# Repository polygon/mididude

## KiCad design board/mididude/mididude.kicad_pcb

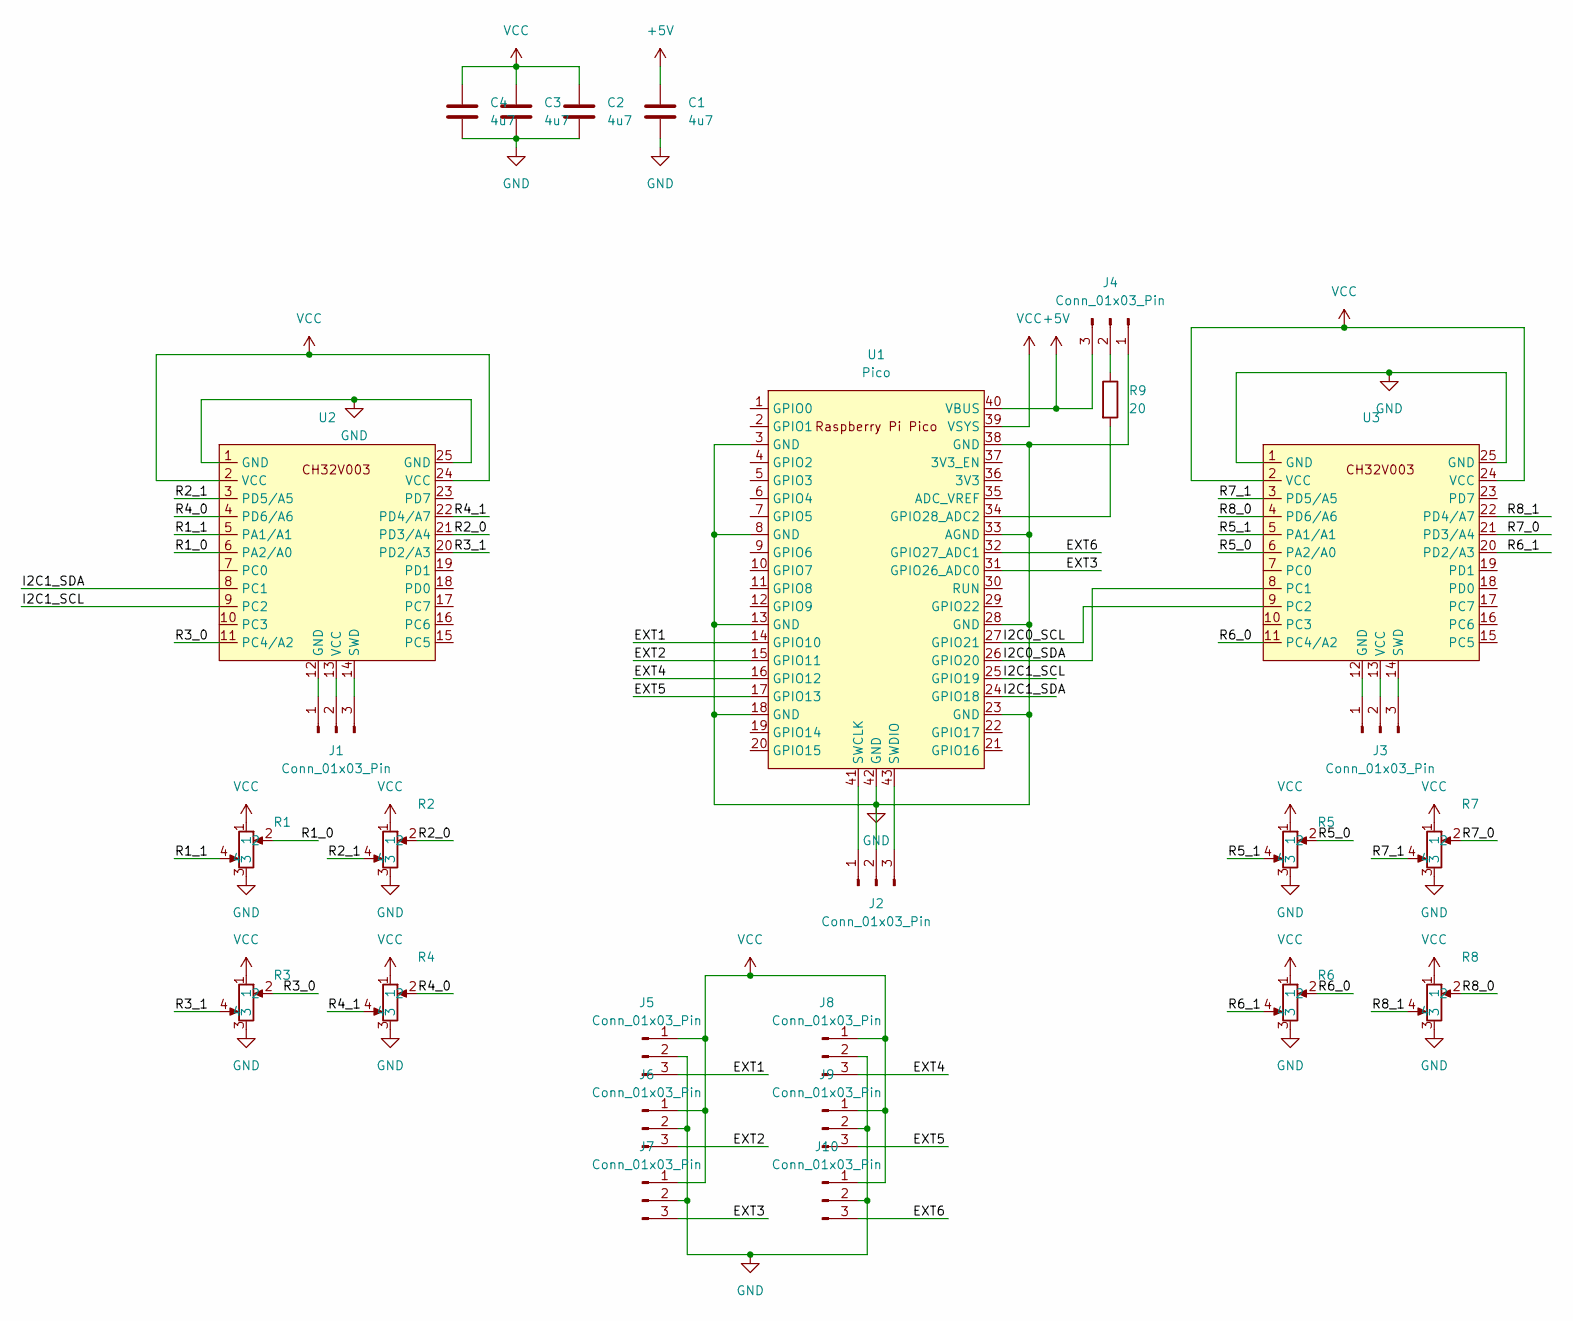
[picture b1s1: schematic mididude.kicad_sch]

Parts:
C1, C2, C3, C4: 4u7; C_0805_2012Metric_Pad1.18x1.45mm_HandSolder
J1, J2, J3, J4, J5, J6, J7, J8, J9, J10: Conn_01x03_Pin; PinHeader_1x03_P2.54mm_Vertical
R1, R2, R3, R4, R5, R6, R7, R8: Endless_potentiometer
R9: 20; R_0603_1608Metric_Pad0.98x0.95mm_HandSolder
U1: Pico; RPi_Pico_SMD_TH
U2, U3: CH32FV003 F1772

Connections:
+5V: C1.1, J4.3, U1.40 (VBUS)
/EXT1: J5.3, U1.14 (GPIO10)
/EXT2: J6.3, U1.15 (GPIO11)
/EXT3: J7.3, U1.31 (GPIO26_ADC0)
/EXT4: J8.3, U1.16 (GPIO12)
/EXT5: J9.3, U1.17 (GPIO13)
/EXT6: J10.3, U1.32 (GPIO27_ADC1)
/I2C0_SCL: U1.27 (GPIO21), U3.9 (PC2)
/I2C0_SDA: U1.26 (GPIO20), U3.8 (PC1)
/I2C1_SCL: U1.25 (GPIO19), U2.9 (PC2)
/I2C1_SDA: U1.24 (GPIO18), U2.8 (PC1)
/R1_0: R1.2, U2.6 (PA2/A0)
/R1_1: R1.4, U2.5 (PA1/A1)
/R2_0: R2.2, U2.21 (PD3/A4)
/R2_1: R2.4, U2.3 (PD5/A5)
/R3_0: R3.2, U2.11 (PC4/A2)
/R3_1: R3.4, U2.20 (PD2/A3)
/R4_0: R4.2, U2.4 (PD6/A6)
/R4_1: R4.4, U2.22 (PD4/A7)
/R5_0: R5.2, U3.6 (PA2/A0)
/R5_1: R5.4, U3.5 (PA1/A1)
/R6_0: R6.2, U3.11 (PC4/A2)
/R6_1: R6.4, U3.20 (PD2/A3)
/R7_0: R7.2, U3.21 (PD3/A4)
/R7_1: R7.4, U3.3 (PD5/A5)
/R8_0: R8.2, U3.4 (PD6/A6)
/R8_1: R8.4, U3.22 (PD4/A7)
GND: C1.2, C2.2, C3.2, C4.2, J2.2, J4.1, J5.2, J6.2, J7.2, J8.2, J9.2, J10.2, R1.3, R2.3, R3.3, R4.3, R5.3, R6.3, R7.3, R8.3, U1.3 (GND), U1.8 (GND), U1.13 (GND), U1.18 (GND), U1.23 (GND), U1.28 (GND), U1.33 (AGND), U1.38 (GND), U1.42 (GND), U2.1 (GND), U2.25 (GND), U3.1 (GND), U3.25 (GND)
unnamed: J1.1, U2.12 (GND)
unnamed: J1.2, U2.13 (VCC)
unnamed: J1.3, U2.14 (SWD)
unnamed: J2.1, U1.41 (SWCLK)
unnamed: J2.3, U1.43 (SWDIO)
unnamed: J3.1, U3.12 (GND)
unnamed: J3.2, U3.13 (VCC)
unnamed: J3.3, U3.14 (SWD)
unnamed: J4.2, R9.1
unnamed: R9.2, U1.34 (GPIO28_ADC2)
VCC: C2.1, C3.1, C4.1, J5.1, J6.1, J7.1, J8.1, J9.1, J10.1, R1.1, R2.1, R3.1, R4.1, R5.1, R6.1, R7.1, R8.1, U1.39 (VSYS), U2.2 (VCC), U2.24 (VCC), U3.2 (VCC), U3.24 (VCC)

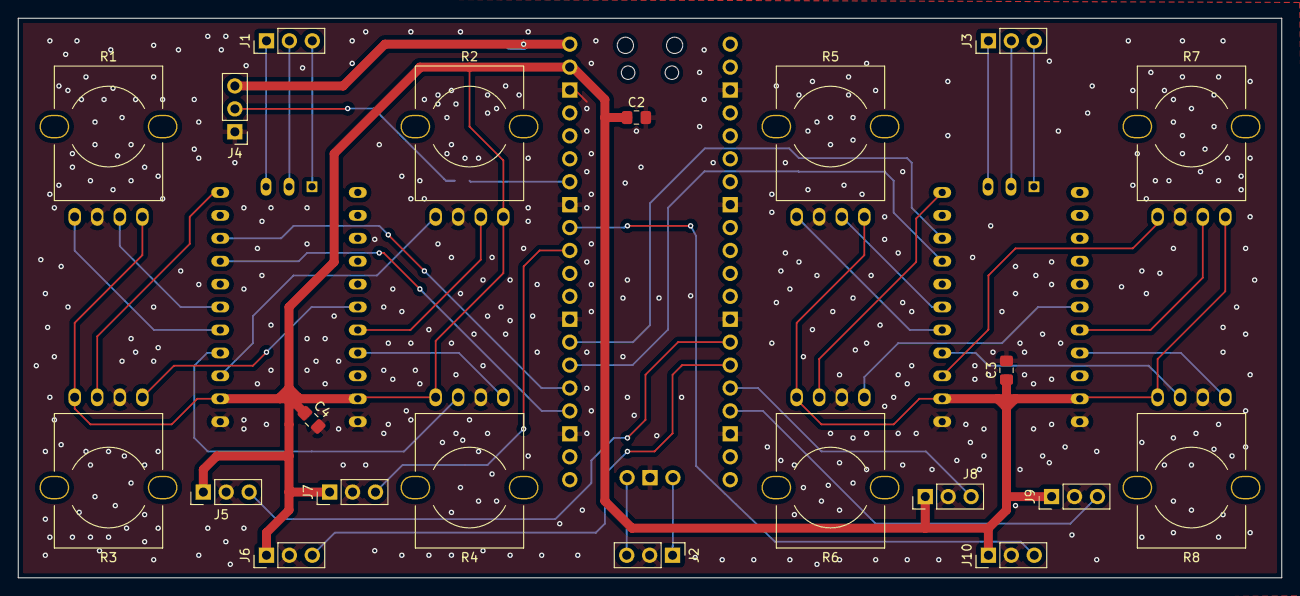
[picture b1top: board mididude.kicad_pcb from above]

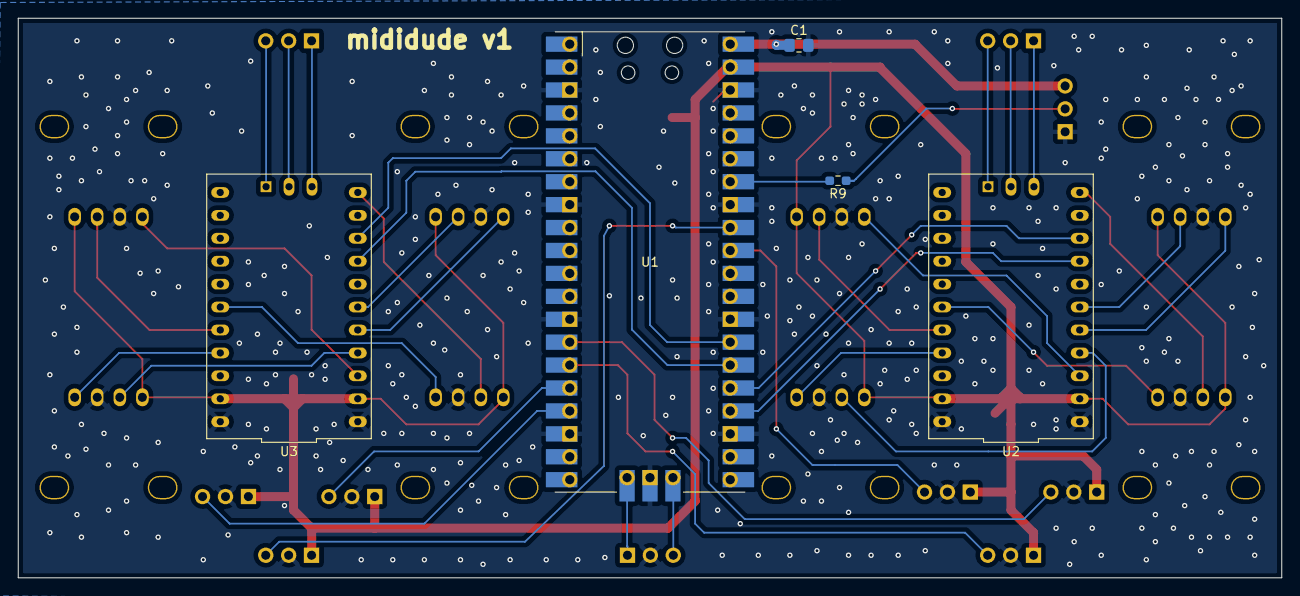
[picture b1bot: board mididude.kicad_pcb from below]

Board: 2 copper layers, 140.0 x 62.0 mm, 26 parts (5 on the bottom side), 39 nets.

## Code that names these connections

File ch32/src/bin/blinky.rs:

#![no_std]
#![no_main]
#![feature(type_alias_impl_trait)]
#![feature(impl_trait_in_assoc_type)]
#![feature(iterator_try_collect)]

use ch32_hal::adc::{Adc, AnyAdcChannel};
use ch32_hal::bind_interrupts;
use ch32_hal::peripherals::ADC1;
use ch32_hal::{self as hal, adc::AdcChannel};
use core::fmt::Write;
use core::task::Poll;
use embedded_graphics::primitives::ellipse;
use hal::usart::UartTx;

use mididude_adc::i2c_device::{Command, Config, I2cSlave};

struct InfPoti {
    in0: AnyAdcChannel<ADC1>,
    in1: AnyAdcChannel<ADC1>,
}

impl InfPoti {
    pub fn measure(&mut self, adc: &mut Adc<'_, ADC1>) -> (i16, i16) {
        let a1 = adc.convert(&mut self.in0, hal::adc::SampleTime::CYCLES73) & 0x0fff;
        let a2 = adc.convert(&mut self.in1, hal::adc::SampleTime::CYCLES73) & 0x0fff;
        (a1 as i16, a2 as i16)
    }
}

struct Converter {
    cutoff: i16,
    transition: i16,
    wrap_range: i16,
}

impl Default for Converter {
    fn default() -> Self {
        Self {
            cutoff: 128,
            transition: 16,
            wrap_range: 32,
        }
    }
}

impl Converter {
    pub fn tri_inv(&self, val: i16, offset: i16) -> (i16, i16) {
        let val = val.clamp(0, 1023);
        let p1 = val / 2;
        let p2 = 1024 - p1;
        return (
            (p1 + offset).rem_euclid(1025),
            (p2 + offset).rem_euclid(1025),
        );
    }

    pub fn tri_weight(&self, val: i16) -> f32 {
        let val = val.clamp(0, 1023);
        let diff = val.min(1024 - val);
        if diff < self.cutoff {
            0.0
        } else if diff < self.cutoff + self.transition {
            1.0 - (diff - self.cutoff) as f32 / self.transition as f32
        } else {
            1.0
        }
    }

    pub fn wrap(&self, v: (i16, i16)) -> (i16, i16) {
        if (v.0 <= self.wrap_range) && (v.1 >= 1024 - self.wrap_range) {
            (v.0, v.1 - 1024)
        } else if (v.1 <= self.wrap_range) && (v.0 >= 1024 - self.wrap_range) {
            (v.0 - 1024, v.1)
        } else {
            v
        }
    }

    pub fn convert(&self, v: (i16, i16)) -> i16 {
        let p1 = self.tri_inv(v.0, 0);
        let w_a = self.tri_weight(v.0);
        let p2 = self.tri_inv(v.1, -256);
        let w_b = self.tri_weight(v.1);
        let diffs = [
            (p1.0 - p2.0).abs(),
            (p1.0 - p2.1).abs(),
            (p1.1 - p2.0).abs(),
            (p1.1 - p2.1).abs(),
        ];
        let (pos_a, pos_b) =
            if (diffs[0] < diffs[1]) && (diffs[0] < diffs[2]) && (diffs[0] < diffs[3]) {
                (p1.0, p2.0)
            } else if (diffs[1] < diffs[2]) && (diffs[1] < diffs[3]) {
                (p1.0, p2.1)
            } else if (diffs[2] < diffs[3]) {
                (p1.1, p2.0)
            } else {
                (p1.1, p2.1)
            };

        let final_pos =
            (((pos_a as f32 * w_a + pos_b as f32 * w_b) / (w_a + w_b)) as i16).rem_euclid(1024);

        final_pos
    }

    pub fn convert_print(&self, v: (i16, i16), uart: &mut impl Write) -> i16 {
        let p1 = self.tri_inv(v.0, 0);
        let w_a = self.tri_weight(v.0);
        let p2 = self.tri_inv(v.1, -256);
        let w_b = self.tri_weight(v.1);
        let diffs = [
            (p1.0 - p2.0).abs(),
            (p1.0 - p2.1).abs(),
            (p1.1 - p2.0).abs(),
            (p1.1 - p2.1).abs(),
        ];
        let (pos_a, pos_b) =
            if (diffs[0] < diffs[1]) && (diffs[0] < diffs[2]) && (diffs[0] < diffs[3]) {
                (p1.0, p2.0)
            } else if (diffs[1] < diffs[2]) && (diffs[1] < diffs[3]) {
                (p1.0, p2.1)
            } else if (diffs[2] < diffs[3]) {
                (p1.1, p2.0)
            } else {
                (p1.1, p2.1)
            };

        let final_pos =
            (((pos_a as f32 * w_a + pos_b as f32 * w_b) / (w_a + w_b)) as i16).rem_euclid(1024);
        writeln!(
            uart,
            //":: {:?} :: {:?}, {:?}, {:?}, {:?}, {:?}, {:?}, {:?}, {:?}\r",
            //final_pos, v.0, v.1, p1, p2, diff_a, diff_b, pos_a, pos_b
            "{:?}, {:?}, {:?}, {:?}, {:?}, {:?}, {:?}, {:?}, {:?}\r",
            v.0, v.1, final_pos, p1.0, p1.1, p2.0, p2.1, pos_a, pos_b
        )
        .unwrap();

        final_pos
    }
}

#[qingke_rt::entry]
fn main() -> ! {
    //hal::debug::SDIPrint::enable();
    let mut config = hal::Config::default();
    config.rcc = hal::rcc::Config::SYSCLK_FREQ_48MHZ_HSI;
    let p = hal::init(config);

    //let mut uart = UartTx::new_blocking(p.USART1, p.PC0, Default::default()).unwrap();

    let mut config = Config::default();
    config.addr = 0x10;
    config.general_call = false;

    let i2c = I2cSlave::new(p.I2C1, config, p.PC1, p.PC2);

    let mut adc = hal::adc::Adc::new(p.ADC1, Default::default());

    let mut potis = [
        InfPoti {
            in0: p.PA2.degrade_adc(),
            in1: p.PA1.degrade_adc(),
        },
        InfPoti {
            in0: p.PC4.degrade_adc(),
            in1: p.PD2.degrade_adc(),
        },
        InfPoti {
            in0: p.PD3.degrade_adc(),
            in1: p.PD5.degrade_adc(),
        },
        InfPoti {
            in0: p.PD6.degrade_adc(),
            in1: p.PD4.degrade_adc(),
        },
    ];

    let converter = Converter::default();

    loop {
        let mut listen = i2c.listen();
        loop {
            if let Poll::Ready(res) = listen() {
                match res {
                    Ok(Command::Read) => {
                        let positions = [
                            converter.convert(potis[0].measure(&mut adc)),
                            converter.convert(potis[1].measure(&mut adc)),
                            converter.convert(potis[2].measure(&mut adc)),
                            converter.convert(potis[3].measure(&mut adc)),
                        ];

                        let mut val: [u8; 8] = [0; 8];
                        val[..2].copy_from_slice(&positions[0].to_le_bytes());
                        val[2..4].copy_from_slice(&positions[1].to_le_bytes());
                        val[4..6].copy_from_slice(&positions[2].to_le_bytes());
                        val[6..].copy_from_slice(&positions[3].to_le_bytes());
                        let mut respond = i2c.respond_to_read(&val, Some(0));
                        loop {
                            if let Poll::Ready(res) = respond() {
                                match res {
                                    /*Ok(_) => (),
                                    Err(e) => writeln!(uart, "Error: {:?}\r", e).unwrap(),*/
                                    _ => (),
                                }
                                break;
                            }
                        }
                    }
                    //Ok(Command::Write(_, buf)) => val = buf[0],
                    //Ok(a) => (), //writeln!(uart, "Ok: {:?}\r", a).unwrap(),
                    /*Ok(Command::Write(_, _)) => (),
                    Ok(a) => writeln!(uart, "I2C: {:?}\r", a).unwrap(),
                    Err(e) => writeln!(uart, "Error: {:?}\r", e).unwrap(),*/
                    _ => (),
                }
                break;
            } else {
                // Timeout
                //writeln!(uart, "Timeout\r").unwrap();
            }
        }
    }
}

use core::panic::PanicInfo;

#[inline(never)]
#[panic_handler]
fn panic(_info: &PanicInfo) -> ! {
    loop {}
}

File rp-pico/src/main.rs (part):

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
    let mut i2c0 = I2C::i2c0(
        pac.I2C0,
        pins.gpio20.reconfigure(),
        pins.gpio21.reconfigure(),
        HertzU32::kHz(400),
        &mut pac.RESETS,
        &clocks.system_clock,
    );
    let mut i2c1 = I2C::i2c1(
        pac.I2C1,
        pins.gpio18.reconfigure(),
        pins.gpio19.reconfigure(),
        HertzU32::kHz(400),
        &mut pac.RESETS,
        &clocks.system_clock,
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
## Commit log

2025-07-19 Mididude Init
    * Board Design
    * CH32 I2C ADC Expander Code
    * Basic USB-MIDI-Device RP-Pico code
2025-07-20 Fix CH32 glitches, improve FW
2025-07-20 Pretty good firmware
2025-07-21 Ensure USB is polled even if nothing moves on the device
2025-07-21 Pretty well usable firmware
2025-07-22 Case
2025-07-23 Whole case, v1
